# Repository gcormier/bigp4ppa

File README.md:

# big p4ppa
A Raspberry Pi 5-channel PWM, PT100 and ADXL345 board. Should work on any Pi2/3/4

I was looking to add on more controllable fans to my 3D printer. The SKR was
maxxed out even just a simple controllable fan, let alone PWM. [Klipper](https://www.klipper3d.org/) supports
multiple MCU's, including the [Raspberry Pi](https://www.klipper3d.org/RPi_microcontroller.html) so adding this to the Pi was a simple way to tackle the problem.

With a bit of spare board space (it was tight) I also fit some space to accommodate
PT100 modules, so I could have a nice place to put mine.

# Features
- Power the Raspberry Pi via the 5V input

   You MUST power the Pi via this board. Do not connect any other power source (USB, PoE hat, battery backup hat) to the Pi when using this board.

- 5 PWM outputs (via MOSFETs with external flyback diodes)
- Independant voltages for each fan - 5V or anything up 24V
- Cutout for a 25mmx25mm fan to cool the Pi if desired
- Support for [Adafruit's PT100 amplifier](https://www.adafruit.com/product/3328) board OR a [PT100 Stepstick](https://github.com/VoronDesign/Voron-Hardware) (available on AliExpress/etc)
- Convenient header for an ADXL345 accelerometer to [measure resonance](https://www.klipper3d.org/Measuring_Resonances.html) in Klipper

## Purchase on Tindie
The design is fully open source, and you are welcome to build this yourself. If you would like to buy a kit or fully assembled version, you can buy it on my Tindie store, <a href="https://www.tindie.com/products/gcormier/big-p4ppa/">Greg's Tinker Town</a>. The kit is exclusive through-hole components.

# How to use
- Put a jumper on the appropriate voltage for each fan
- Connect 5V and Ground
- Connect the other voltage rails you plan on using. Note 12V/24V are just labels. You could supply 16V if you had fans that worked at that voltage for some reason. The maximum voltage is 24V. You need to make sure your power supply can source enough current for all your fans. Don't forget to account for current required by the Pi itself on the 5V supply!
- You can control the fans via the GPIO's as printed on the circuit board
   - Looking at the board, left to right - GPIO12, GPIO13, GPIO18, GPIO26, GPIO23

## Standoffs
The main board itself is rather sturdy, but using standoffs would be an extra measure to keep the board secure.

If using the Adafruit board, standoffs for that board are recommended.

## Power Header
Note that the input header will only accept the smallest (white) ferrules. Unfortunately there is minimal space on the board
to accomodate a larger screw terminal without removing a channel.

# Accelerometer
The header supports either a 2x3 or 2x4 pin header. The 2x4 header can accomadate previously designed 2x4 headers that plugged
directly in the Raspberry Pi header. The two 3V3 pins are linked so you can use either to power the ADXL345.

Note that if you are using a 4-wire thermistor, plugging in the accelerometer could be challenging. You may need to
remove the thermistor temporarily for accelerometer tuning.
## Klipper config
First, give a good read to [Klipper documentation on Raspberry Pi as a secondary MCU](https://www.klipper3d.org/RPi_microcontroller.html)

Then, we can reference the [sample configuration provided](https://github.com/KevinOConnor/klipper/blob/master/config/sample-raspberry-pi.cfg) and come up with the sample config files located in this repository.

## Limits
The board was designed to power fans, not heavy loads or heaters. The designed but un-tested recommendations are a maximum of 750mA per channel, and a total maximum of 3A. Most fans operate between 50mA and 300mA. If you are going beyond this, you would be wise to review the trace widths and measure thermals to ensure you are comfortable with the results.

# Technical Notes
## Serial Bus
The Pi has 2 SPI busses. big p4ppa uses SPI1 for the PT100 board, and SPI0 for the ADXL accelerometer. Note that these pin arrangements are suited to the intended modules, but are otherwise just SPI breakouts if you want to use them for other purposes. Also, if you want to solder a [Pi stacking header](https://www.adafruit.com/product/1979) and use another board on top of this one, you can make a note of which SPI bus your additional board uses and avoid using it on big p4ppa. Fitment is not guaranteed for additional boards stacked on top.

## Pi Fan
Generally speaking it's hard to find 24V fans in 25mm x 25mm size. There are lots of 5V or 12V options. If you choose 5V,
you may wish to run the fan at full speed for electrical noise considerations, as it is sharing the 5V of the Pi. As a result,
choose your fan accordingly rather then buying something too strong and needing PWM to slow it down.

## No NeoPixel?
The SKR 1.4 already supports Neopixel LED's. It had to be cut due to board space.

## Kicad Notes
Apologies for the KiCad layout. To be honest, it feels like KiCad v6 is so close,
I haven't invested much effort. V6 will bundle symbols with the schematic
which will be a huge step forward. Gerber's are there if you want to send them off
to a fab.

## Errata
### v1
- The 5th output (furthest right) labelled GPIO19 is actually GPIO23
- The 4th output labelled GPIO19 is actually GPIO26
- The sample configuration [klipper-v1.cfg](klipper-v1.cfg) uses the correct GPIO numbers
- For reference, left to right, the correct GPIOs are GPIO12, GPIO13, GPIO18, GPIO26, GPIO23

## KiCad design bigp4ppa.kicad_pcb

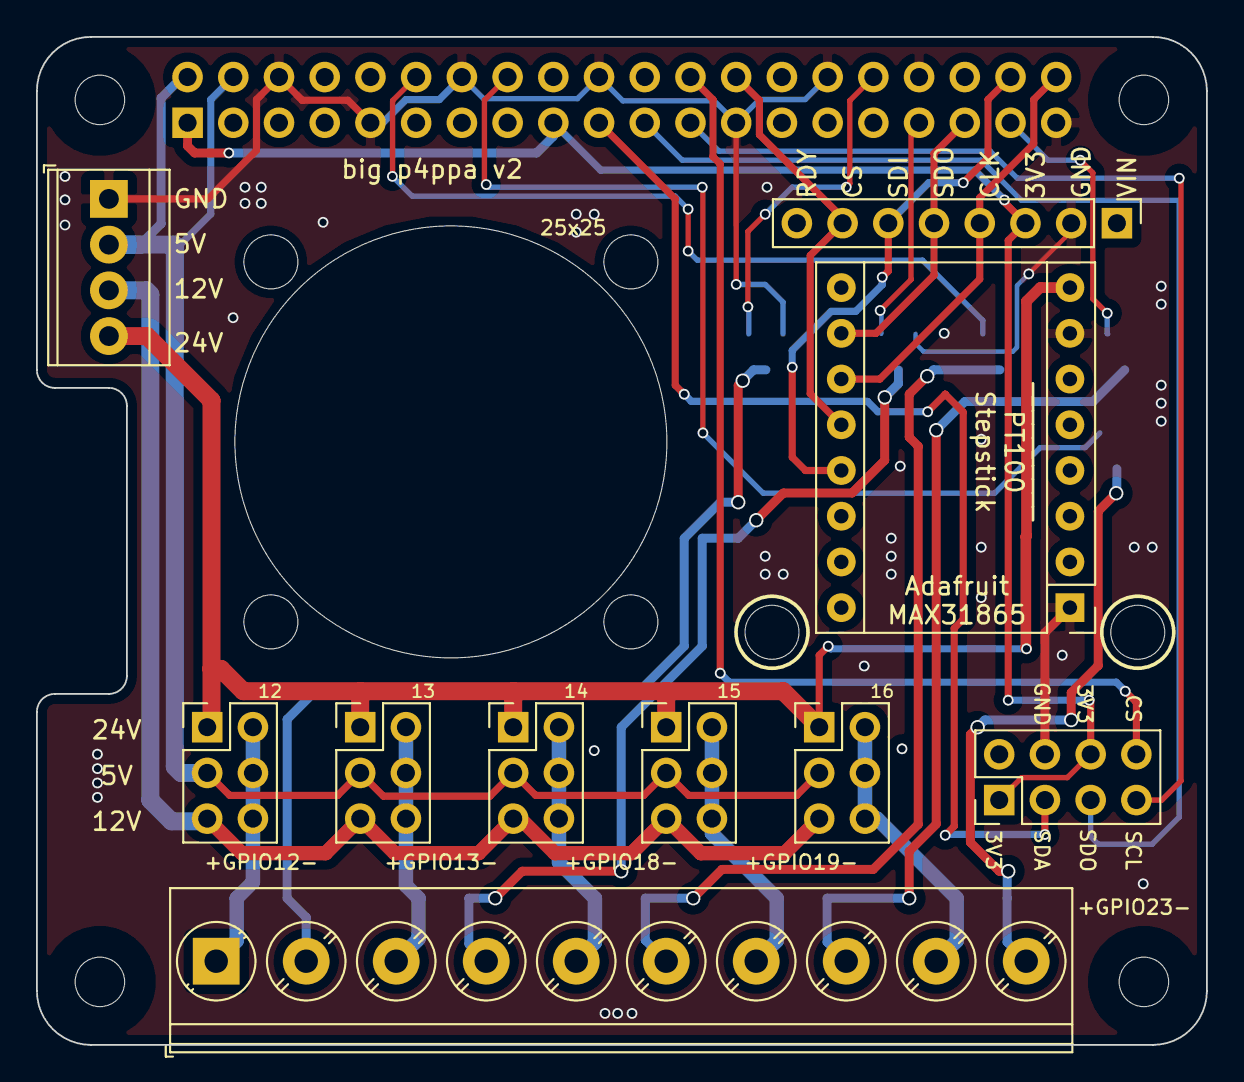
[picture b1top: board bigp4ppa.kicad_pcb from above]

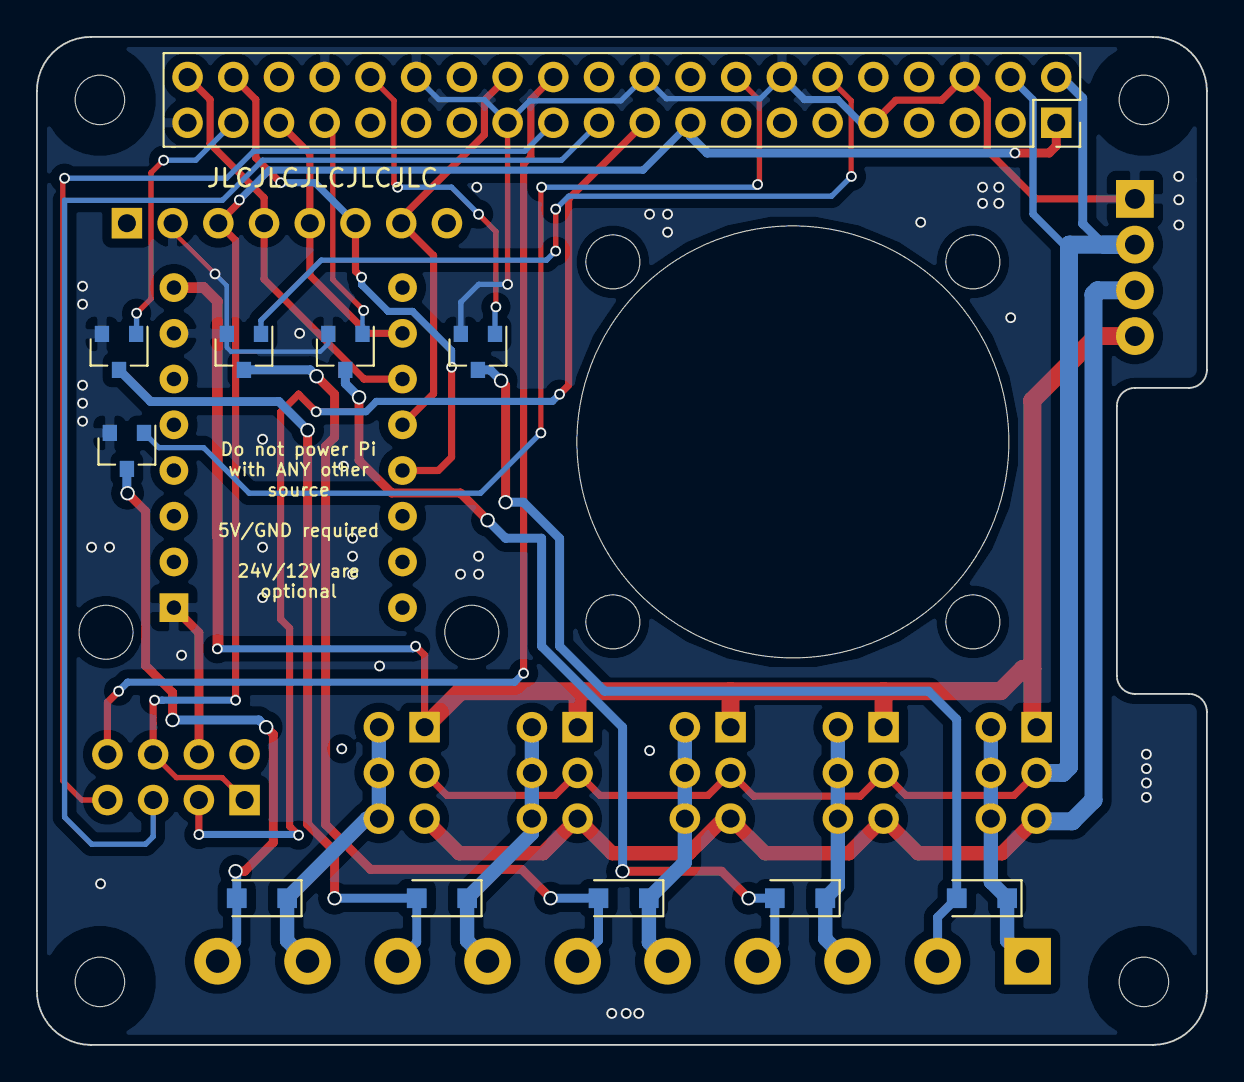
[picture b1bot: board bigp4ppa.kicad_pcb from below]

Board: 2 copper layers, 65.0 x 56.0 mm, 24 parts (11 on the bottom side), 28 nets.

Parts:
25x25: Fan-25x25x10
A1: Pololu_Breakout_A4988; Pololu_Breakout-16_15.2x20.3mm
D1, D2, D3, D4, D5: D; D_SOD-123F
J1: Power Input; TerminalBlock_TE_282834-4_1x04_P2.54mm_Horizontal
J2: Raspberry_Pi; PinSocket_2x20_P2.54mm_Vertical
J3: VOLTAGEFAN; PinHeader_2x03_P2.54mm_Vertical
J4: Output; TerminalBlock_Phoenix_PT-1,5-10-5.0-H_1x10_P5.00mm_Horizont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
J8: MAX13865; PinHeader_1x08_P2.54mm_Vertical
J11: VOLTAGE19; PinHeader_2x03_P2.54mm_Vertical
J12: VOLTAGE12; PinHeader_2x03_P2.54mm_Vertical
J13: VOLTAGE13; PinHeader_2x03_P2.54mm_Vertical
J14: VOLTAGE18; PinHeader_2x03_P2.54mm_Vertical
J15: ADXL345; PinHeader_2x04_P2.54mm_Vertical
Q1, Q3, Q4, Q5, Q6: AO3402; SOT-23
U$18, U$19: H; MOUNTINGHOLE_2.5_PLATED

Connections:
+3V3: J2.1, J2.17, J8.3, J15.1, J15.6
+5V: J1.2, J2.2, J2.4, J3.3, J11.3, J12.3, J13.3, J14.3
+12V: J1.3, J3.5, J11.5, J12.5, J13.5, J14.5
+24V: A1.8, J1.4, J3.1, J11.1, J12.1, J13.1, J14.1
/GPIO12+: D1.1, J4.1, J12.2, J12.4, J12.6
/GPIO12-: D1.2, J4.2, Q3.3
/GPIO13+: D2.1, J4.3, J13.2, J13.4, J13.6
/GPIO13-: D2.2, J4.4, Q5.3
/GPIO18+: D3.1, J4.5, J14.2, J14.4, J14.6
/GPIO18-: D3.2, J4.6, Q4.3
/GPIO19+: D4.1, J4.7, J11.2, J11.4, J11.6
/GPIO19-: D4.2, J4.8, Q6.3
/GPIO23+: D5.1, J3.2, J3.4, J3.6, J4.9
/GPIO23-: D5.2, J4.10, Q1.3
ADXL_CS: J2.24, J15.8
ADXL_SCL: J2.23, J15.7
ADXL_SDA: J2.19, J15.3
ADXL_SDO: J2.21, J15.5
GND: A1.1, A1.7, J1.1, J2.6, J2.9, J2.14, J2.20, J2.25, J2.30, J2.34, J2.39, J8.2, J15.4, Q1.2, Q3.2, Q4.2, Q5.2, Q6.2
GPIO12: J2.32, Q3.1
GPIO13: J2.33, Q5.1
GPIO18: J2.12, Q4.1
GPIO19: J2.37, Q6.1
GPIO23: J2.16, Q1.1
MAX_CLK: A1.11, J2.40, J8.4
MAX_CS: A1.12, J2.26, J8.7
MAX_SDI: A1.13, J2.38, J8.6
MAX_SDO: A1.10, J2.35, J8.5

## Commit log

2021-03-17 initial
2021-03-17 love markdown
2021-03-17 bye bye markdown imagae
2021-03-17 crop
2021-03-17 moar big
2021-03-17 a word
2021-03-18 tindie link
2021-03-19 notes, pics, sample config
2021-03-19 pi fan note
2021-03-19 re-iterate proper gpio's in errata
2022-11-21 updates and actions
